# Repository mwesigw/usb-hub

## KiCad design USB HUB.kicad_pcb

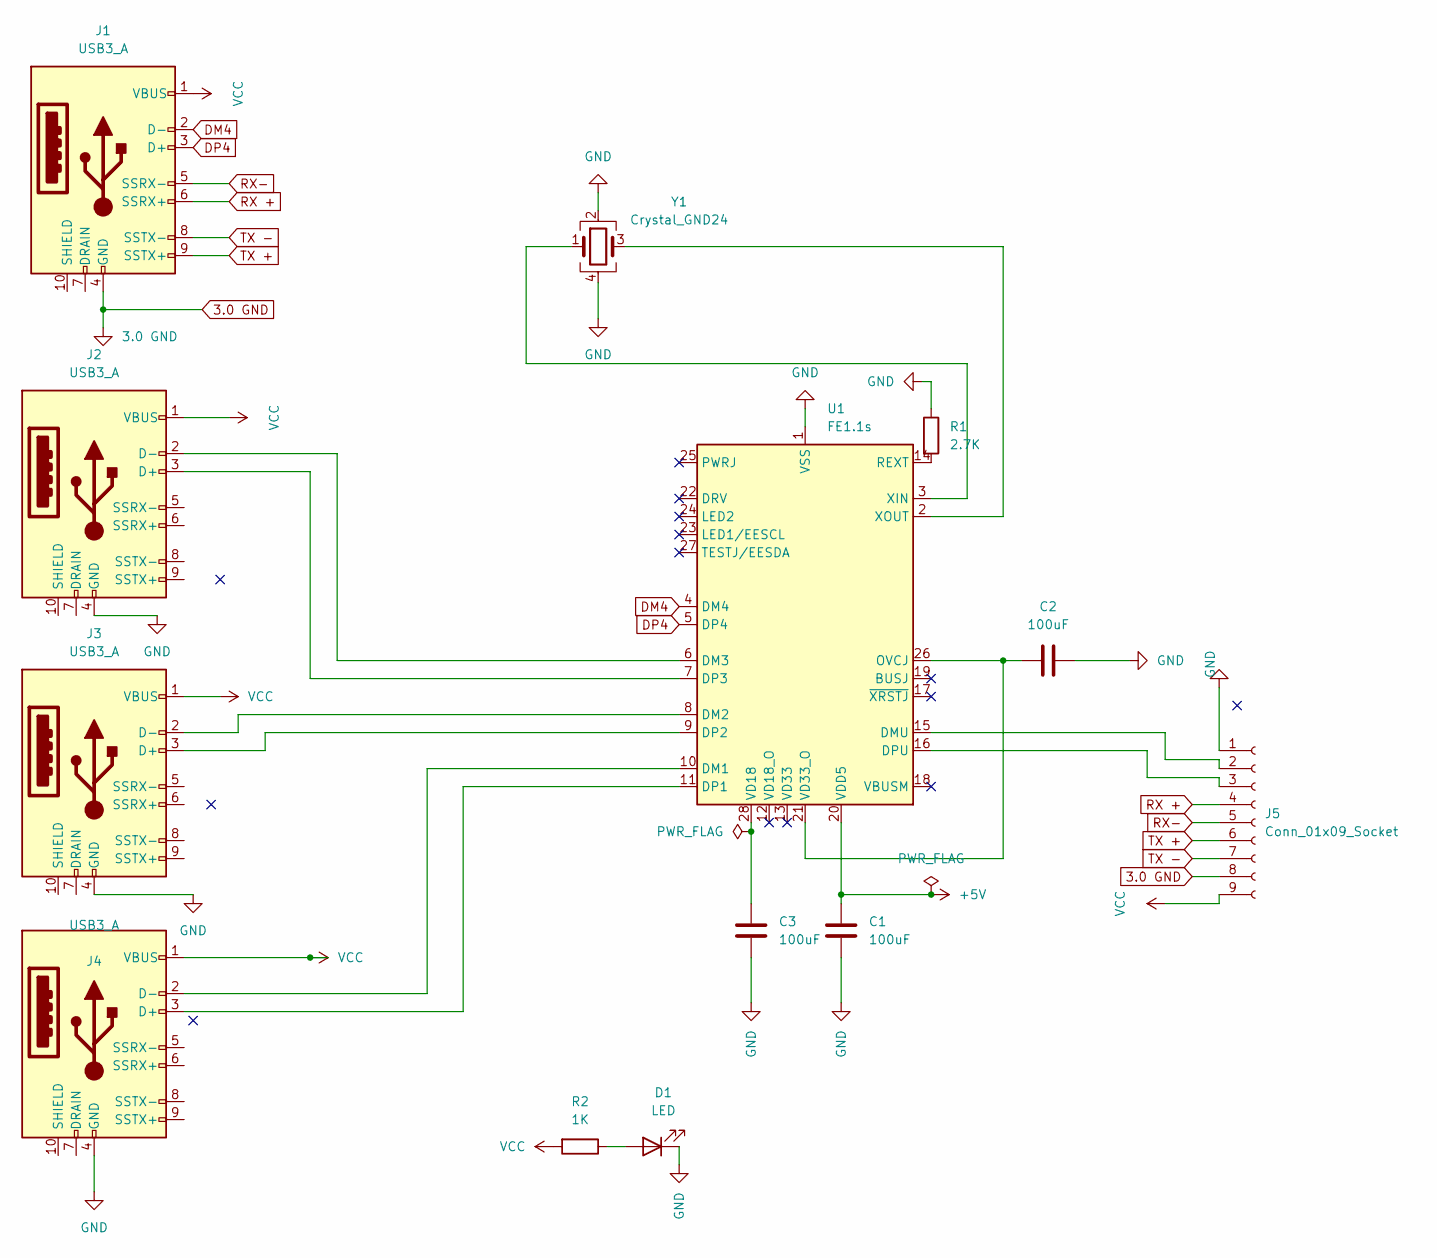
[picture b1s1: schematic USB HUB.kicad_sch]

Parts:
C1, C2, C3: 100uF; C_0402_1005Metric_Pad0.74x0.62mm_HandSolder
D1: LED; LED_D3.0mm_Clear
J1, J2, J3, J4: USB3_A; BEL_SS-52000-004
J5: Conn_01x09_Socket; PinSocket_1x09_P2.54mm_Vertical
R1: 2.7K; R_1206_3216Metric_Pad1.30x1.75mm_HandSolder
R2: 1K; R_1206_3216Metric_Pad1.30x1.75mm_HandSolder
U1: FE1.1s; SSOP-28_3.9x9.9mm_P0.635mm
Y1: Crystal_GND24; Oscillator_SMD_Abracon_ASE-4Pin_3.2x2.5mm_HandSoldering

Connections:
3.0 GND: J1.4 (GND), J5.8
+5V: C1.1, U1.20 (VDD5)
DM4: J1.2 (D-), U1.4 (DM4)
DP4: J1.3 (D+), U1.5 (DP4)
GND: C1.2, C2.2, C3.2, D1.1 (K), J2.4 (GND), J3.4 (GND), J4.4 (GND), J5.1, R1.1, U1.1 (VSS), Y1.2, Y1.4
unnamed: D1.2 (A), R2.1
unnamed: J2.3 (D+), U1.7 (DP3)
unnamed: J2.2 (D-), U1.6 (DM3)
unnamed: J3.3 (D+), U1.9 (DP2)
unnamed: J3.2 (D-), U1.8 (DM2)
unnamed: J4.3 (D+), U1.11 (DP1)
unnamed: J4.2 (D-), U1.10 (DM1)
unnamed: J5.2, U1.15 (DMU)
unnamed: J5.3, U1.16 (DPU)
unnamed: C2.1, U1.21 (VD33_O), U1.26 (OVCJ)
unnamed: R1.2, U1.14 (REXT)
unnamed: C3.1, U1.28 (VD18)
unnamed: U1.3 (XIN), Y1.1
unnamed: U1.2 (XOUT), Y1.3
RX +: J1.6 (SSRX+), J5.4
RX-: J1.5 (SSRX-), J5.5
TX +: J1.9 (SSTX+), J5.6
TX -: J1.8 (SSTX-), J5.7
VCC: J1.1 (VBUS), J2.1 (VBUS), J3.1 (VBUS), J4.1 (VBUS), J5.9, R2.2

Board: 2 copper layers, 13 parts (7 on the bottom side), 24 nets, no tracks yet.

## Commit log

2024-11-06 first init
2024-11-06 changed foot print for connector and foot prints for capacitors to smaller size, placed components in perfect positions
2024-11-06 just saved file
2024-11-06 fix 2
2024-11-06 Hello
2024-11-06 Saved
2024-11-06 i routed
2024-11-06 changed oscillator position
2024-11-06 Test
2024-11-06 moved crystal oscillator
